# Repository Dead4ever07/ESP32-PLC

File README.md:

# ESP32-PLC
My first simple PLC built around an ESP32-S3 to control multiple devices at 230V.

The project was designed to work with an touch LCD. Of course a lot of options are open with this project and allot can be made. Either a small dashboard to control heating elements or to control lighting points.

Here is a picture of it:

If you think it's interesting please give it a start <3.

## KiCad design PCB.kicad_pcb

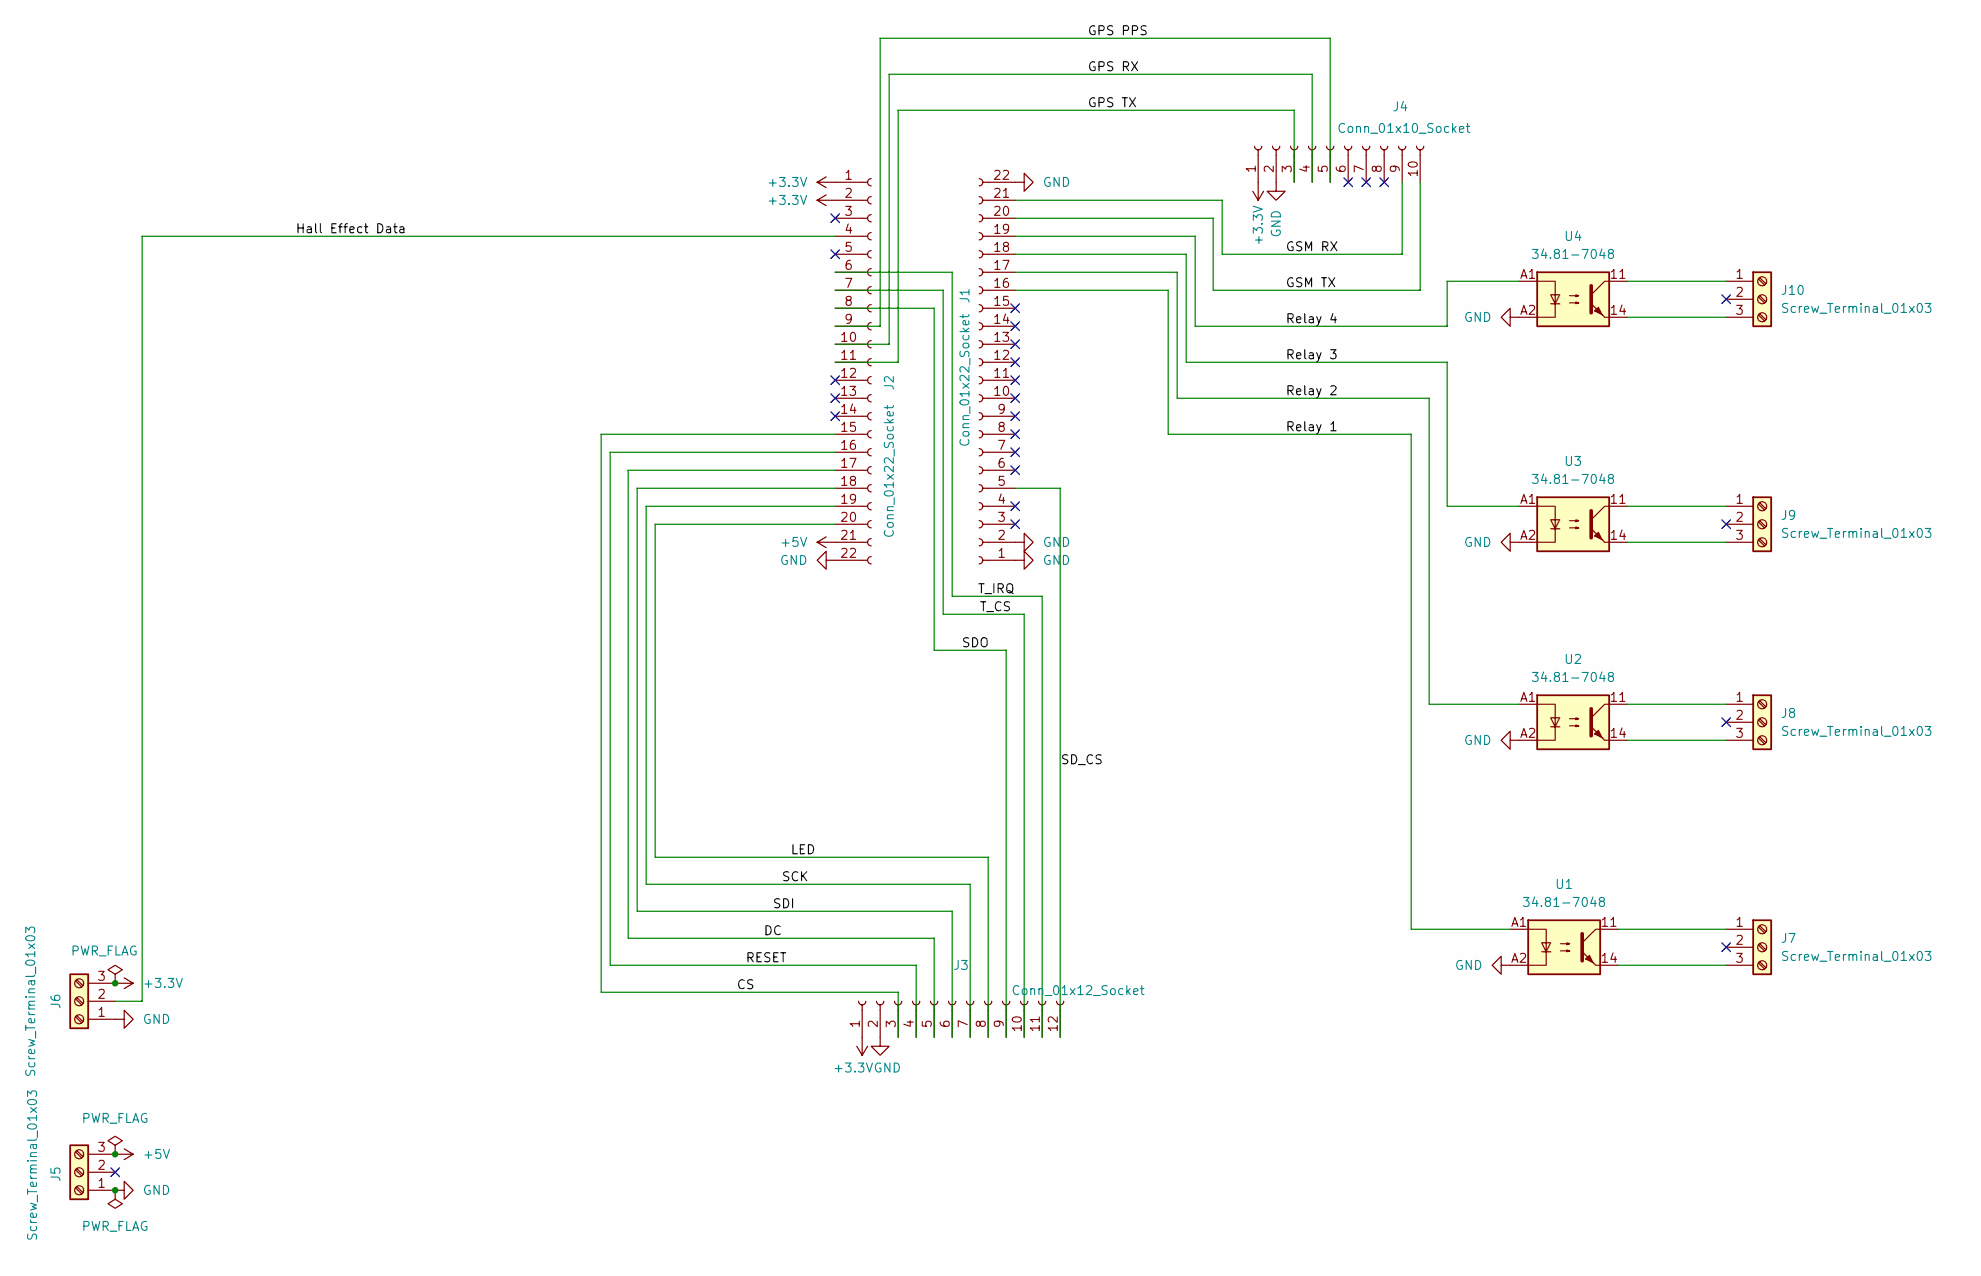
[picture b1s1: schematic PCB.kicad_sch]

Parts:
J1: Conn_01x22_Socket; PinSocket_1x22_P2.54mm_Vertical
J2: Conn_01x22_Socket; PinHeader_1x22_P2.54mm_Vertical
J3: Conn_01x12_Socket; PinHeader_1x12_P2.54mm_Vertical
J4: Conn_01x10_Socket; PinHeader_1x10_P2.54mm_Vertical
J5, J6, J7, J8, J9, J10: Screw_Terminal_01x03; TerminalBlock_Phoenix_MKDS-1,5-3-5.08_1x03_P5.08mm_Horizont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
U1, U2, U3, U4: 34.81-7048; Finder_34.81

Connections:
+3.3V: J2.1, J2.2, J3.1, J4.1, J6.3
+5V: J2.21, J5.3
/CS: J2.15, J3.3
/DC: J2.17, J3.5
/GPS PPS: J2.9, J4.5
/GPS RX: J2.10, J4.4
/GPS TX: J2.11, J4.3
/GSM RX: J1.21, J4.9
/GSM TX: J1.20, J4.10
/Hall Effect Data: J2.4, J6.2
/LED: J2.20, J3.8
/RESET: J2.16, J3.4
/Relay 1: J1.16, U1.A1
/Relay 2: J1.17, U2.A1
/Relay 3: J1.18, U3.A1
/Relay 4: J1.19, U4.A1
/SCK: J2.19, J3.7
/SDI: J2.18, J3.6
/SDO: J2.8, J3.9
/SD_CS: J1.5, J3.12
/T_CS: J2.7, J3.10
/T_IRQ: J2.6, J3.11
GND: J1.1, J1.2, J1.22, J2.22, J3.2, J4.2, J5.1, J6.1, U1.A2, U2.A2, U3.A2, U4.A2
unnamed: J7.1, U1.11
unnamed: J7.3, U1.14
unnamed: J8.1, U2.11
unnamed: J8.3, U2.14
unnamed: J9.1, U3.11
unnamed: J9.3, U3.14
unnamed: J10.1, U4.11
unnamed: J10.3, U4.14

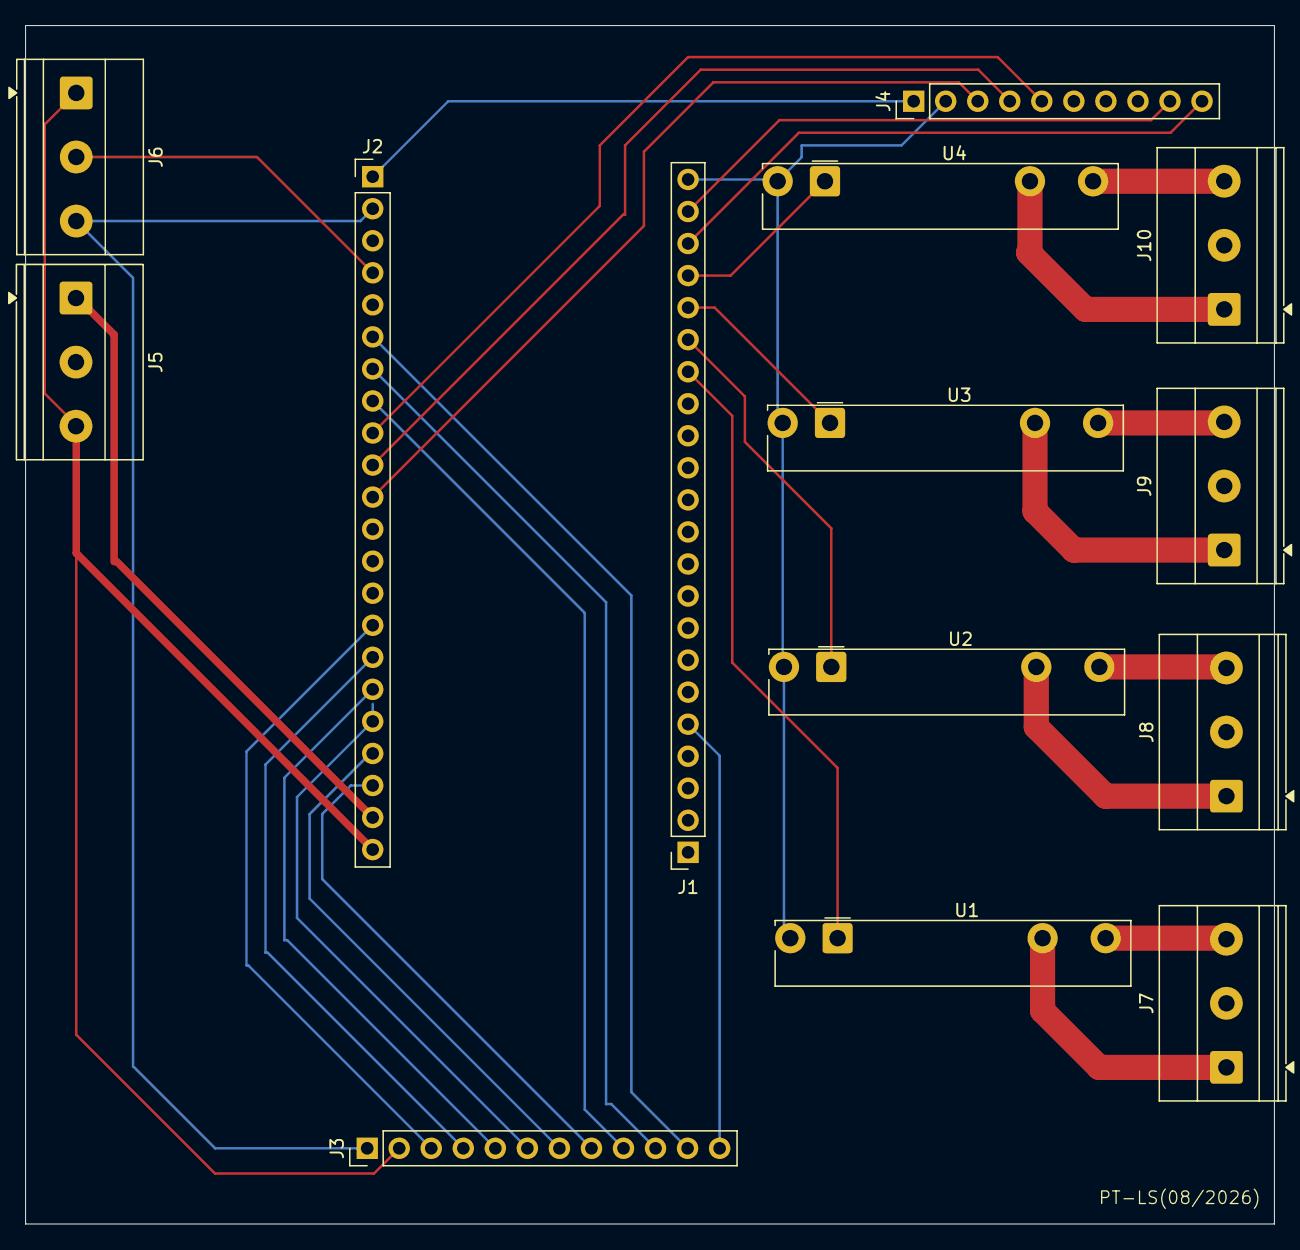
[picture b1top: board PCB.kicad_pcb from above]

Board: 2 copper layers, 99.0 x 95.0 mm, 14 parts (0 on the bottom side), 31 nets.
